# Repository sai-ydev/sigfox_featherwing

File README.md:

# sigfox_featherwing
Sigfox Featherwing

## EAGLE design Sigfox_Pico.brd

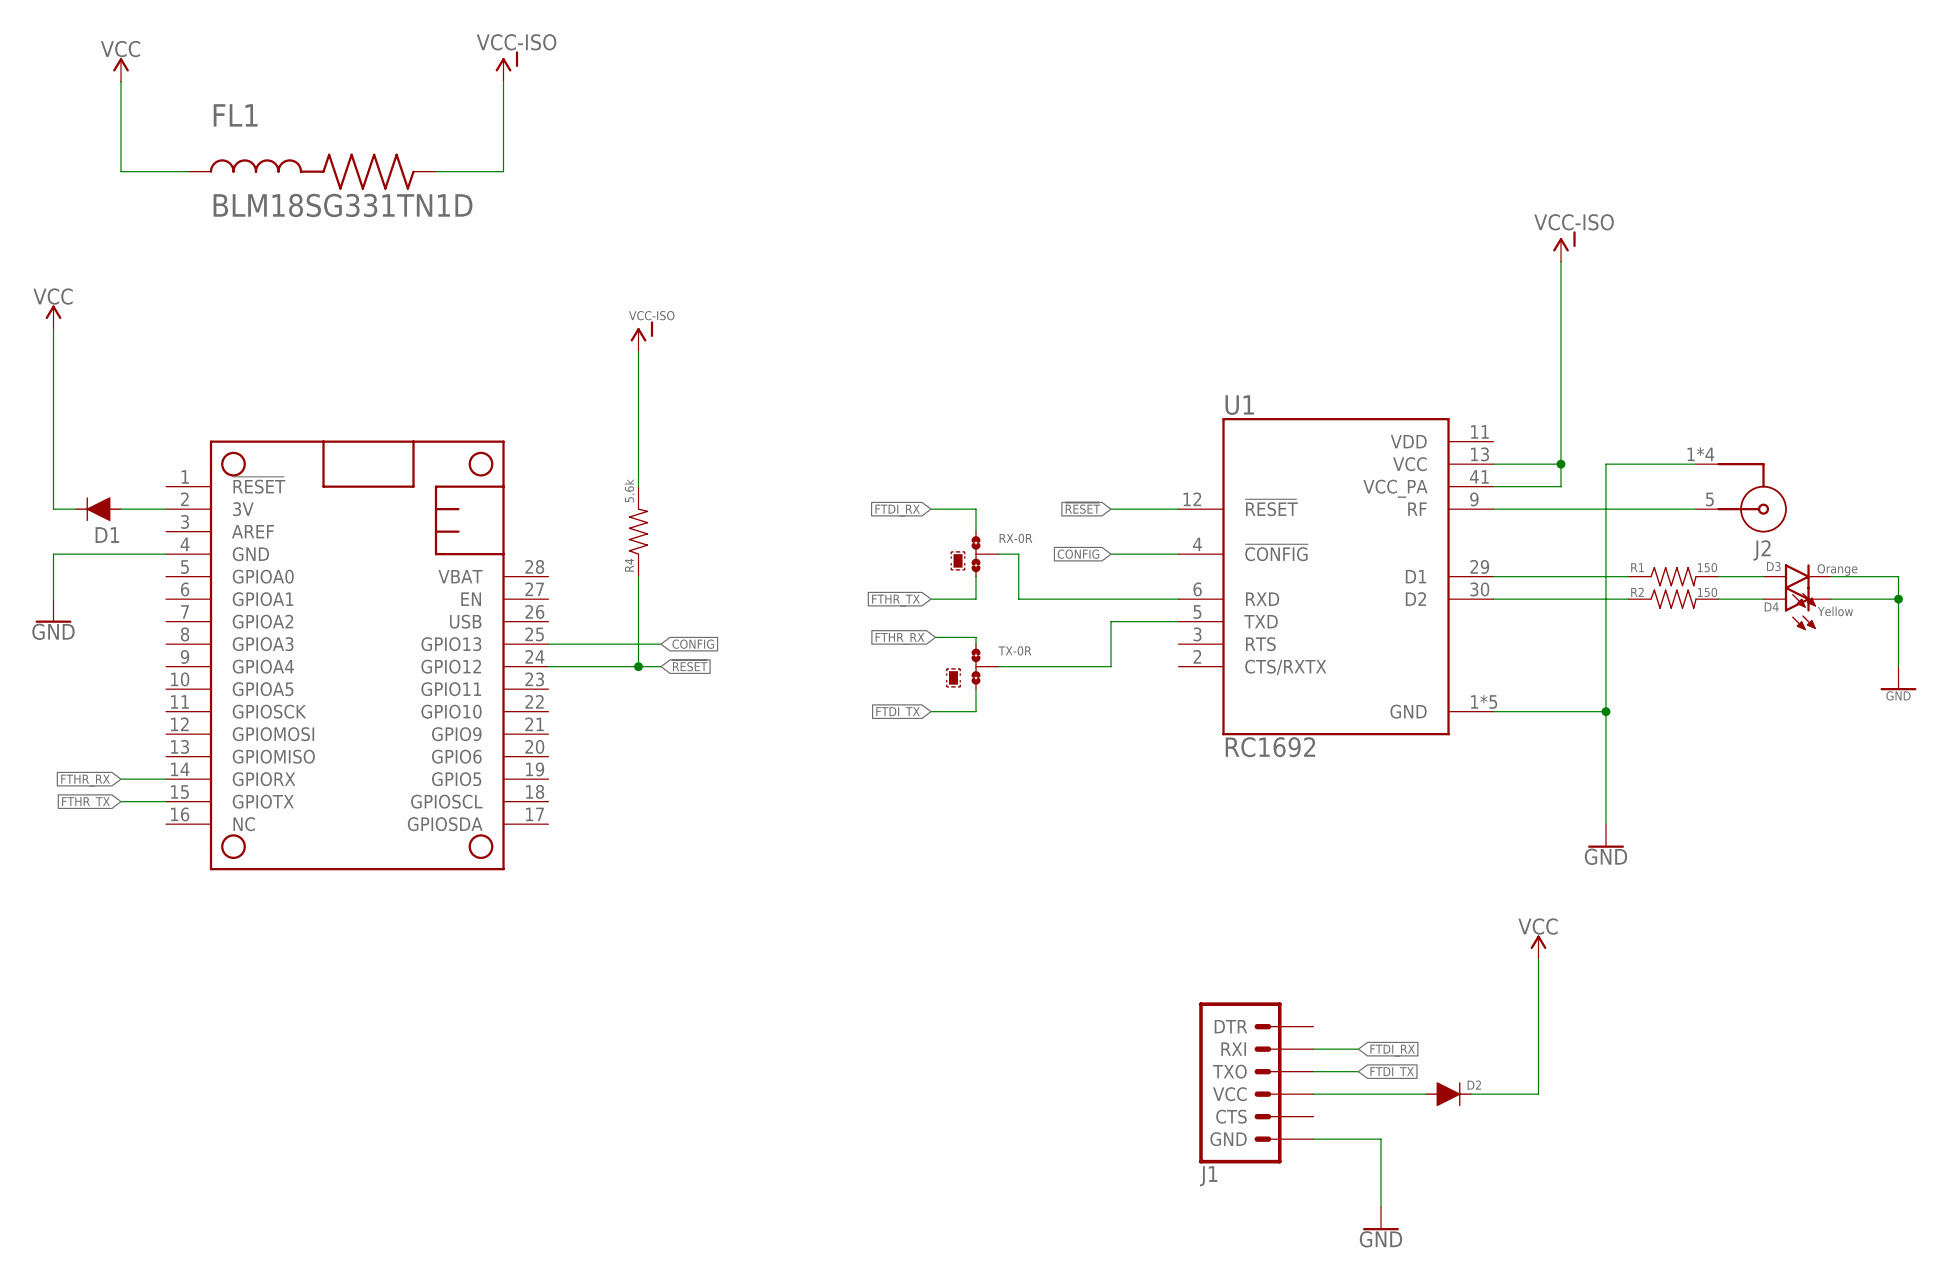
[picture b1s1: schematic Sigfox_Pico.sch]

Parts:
D1, D2: 250mA/100V; SOD-323
D3: Orange; LED-0603
D4: Yellow; LED-0603
FL1: BLM18SG331TN1D; BEADC1608X65N
J1: 6_PIN_SERIAL_TARGETSILK; 6_PIN_SERIAL_TARGET_SIDE_W_SILK
J2: 63012002124503
MS1: FEATHERWING
R1, R2: 150; 0603
R4: 5.6k; 0603
RX: 0R-JUMPB; B0R-JMP
TX: 0R-JUMPB; B0R-JMP
U1: RC1692; MODULE_RC1682-SIG

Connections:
3V: D1.A, MS1.2 (3V)
!RESET: MS1.24 (GPIO12), R4.1, U1.12 (!RESET)
CONFIG: MS1.25 (GPIO13), U1.4 (!CONFIG)
FTDI_RX: J1.P$3 (RXI), RX.1
FTDI_TX: J1.P$2 (TXO), TX.3
FTHR_RX: MS1.14 (GPIORX), TX.1
FTHR_TX: MS1.15 (GPIOTX), RX.3
GND: D3.C, D4.C, J1.P$6 (GND), J2.1 (2), J2.2, J2.3 (2), J2.4 (2), MS1.4 (GND), U1.1 (GND), U1.7 (GND), U1.8 (GND), U1.10 (GND), U1.14 (GND)
unnamed: J2.5 (1), U1.9 (RF)
unnamed: D2.A, J1.P$4 (VCC)
unnamed: RX.2, U1.6 (RXD)
unnamed: TX.2, U1.5 (TXD)
unnamed: R1.1, U1.29 (D1)
unnamed: R2.1, U1.30 (D2)
unnamed: D3.A, R1.2
unnamed: D4.A, R2.2
VCC: D1.C, D2.C, FL1.1
VCC-ISO: FL1.2, R4.2, U1.13 (VCC), U1.41 (VCC_PA)
VDD: U1.11 (VDD)

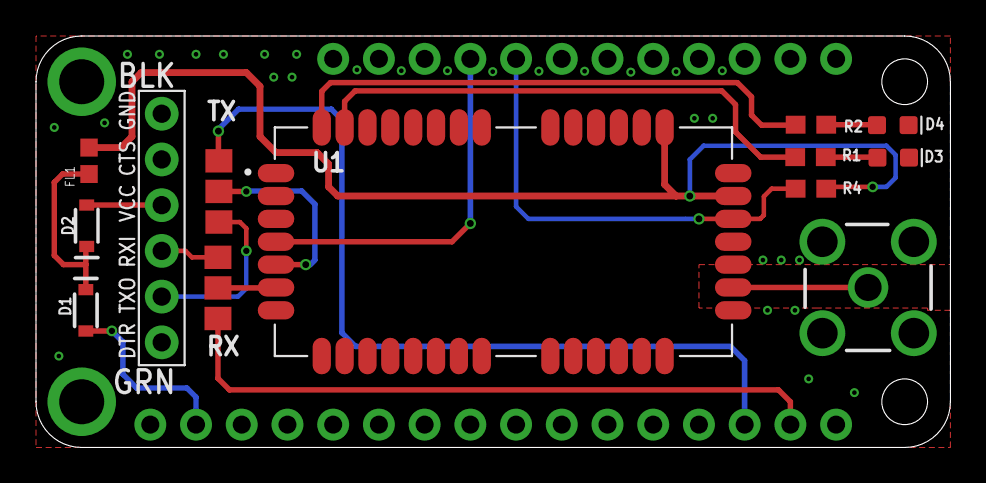
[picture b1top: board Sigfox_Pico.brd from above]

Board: 2 copper layers, 50.8 x 22.9 mm, 14 parts (0 on the bottom side), 18 nets.

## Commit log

2019-12-25 Adding Sigfox featherwing files
2020-01-04 CHanging RX and TX lines on sigfox board
2020-01-14 RP-SMA Check-in
2020-02-26 Check in Sigfox binary files
2021-11-29 Check-in

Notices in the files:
parts and their libraries:
SparkFun-Connectors: Licensing: Creative Commons ShareAlike 4.0 International - https://creativecommons.org/licenses/by-sa/4.0
